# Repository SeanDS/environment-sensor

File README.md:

# environment-sensor
Ethernet-enabled dust particle, temperature and humidity sensor module

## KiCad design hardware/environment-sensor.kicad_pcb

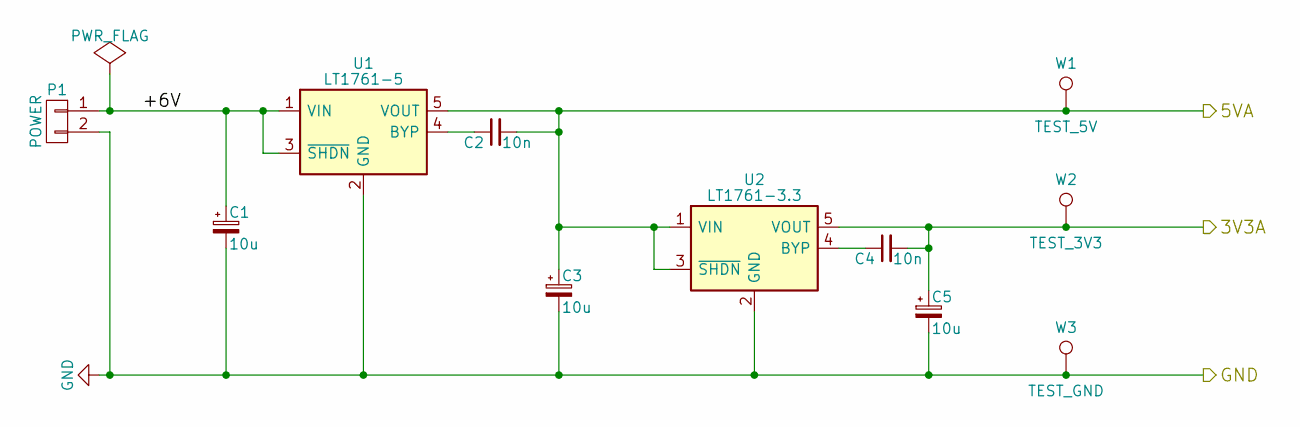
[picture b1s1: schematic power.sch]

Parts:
C1, C3, C5: 10u; C_Radial_D5_L11_P2
C2, C4: 10n; C_1206
P1: POWER; Molex_KK-6410-02_02x2.54mm_Straight
U1: LT1761-5; SOT-23-5
U2: LT1761-3.3; SOT-23-5
W1: TEST_5V; PINTST
W2: TEST_3V3; PINTST
W3: TEST_GND; PINTST

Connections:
/Microcontroller/3V3A: C4.2, C5.1, U2.5 (VOUT), W2.1; also elsewhere on the board
/Microcontroller/5VA: C2.2, C3.1, U1.5 (VOUT), U2.1 (VIN), U2.3 (~SHDN), W1.1; also elsewhere on the board
/Power Supply/+6V: C1.1, P1.1, U1.1 (VIN), U1.3 (~SHDN)
GND: C1.2, C3.2, C5.2, P1.2, U1.2 (GND), U2.2 (GND), W3.1; also elsewhere on the board
unnamed: C2.1, U1.4 (BYP)
unnamed: C4.1, U2.4 (BYP)

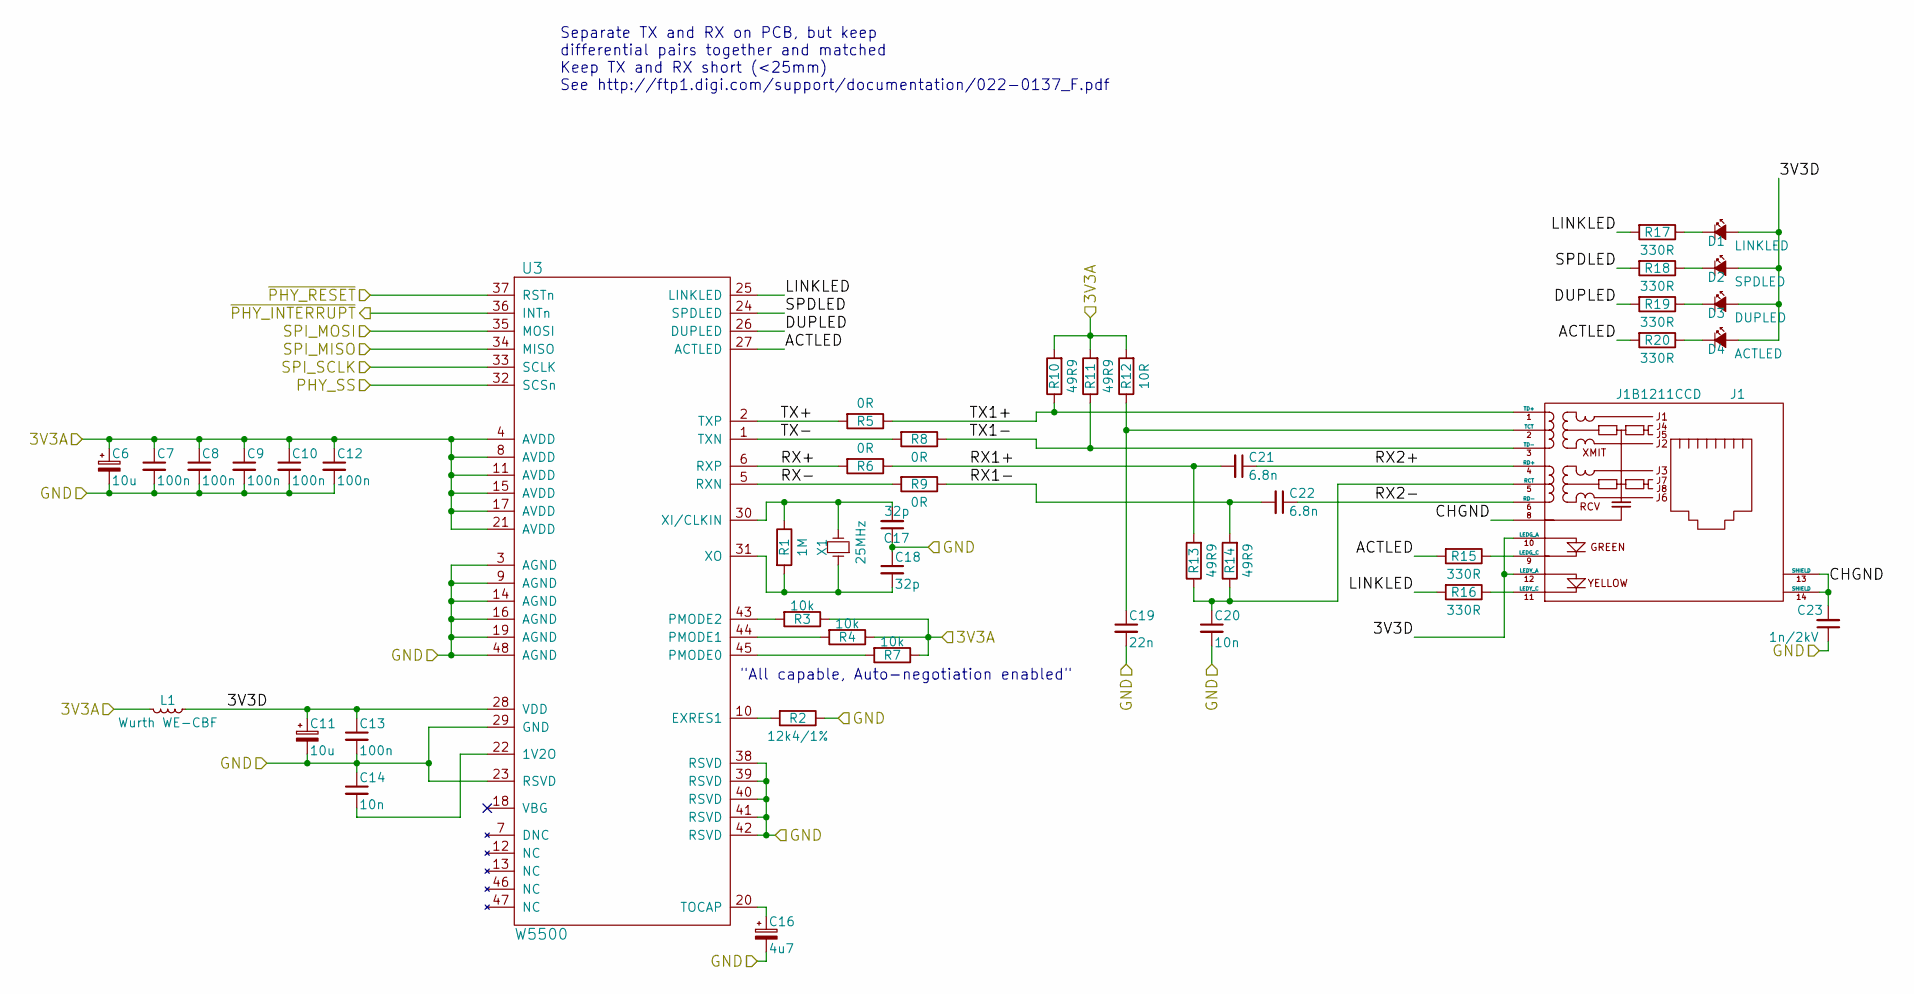
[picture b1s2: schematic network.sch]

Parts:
C6, C11: 10u; C_Radial_D5_L11_P2
C7, C8, C9, C10, C12, C13: 100n; C_1206
C14, C20: 10n; C_1206
C16: 4u7; C_Radial_D5_L11_P2
C17, C18: 32p; C_0603
C19: 22n; C_1206
C21, C22: 6.8n; C_1206
C23: 1n/2kV; C_1206
D1: LINKLED; LED_0805
D2: SPDLED; LED_0805
D3: DUPLED; LED_0805
D4: ACTLED; LED_0805
J1: J1B1211CCD; Cetus_J1B1211CCD
L1: Wurth WE-CBF; Choke_SMD_1206_Standard
R1: 1M; R_1206
R2: 12k4/1%; R_1206
R3, R4, R7: 10k; R_1206
R5, R6, R8, R9: 0R; R_1206
R10, R11, R13, R14: 49R9; R_1206
R12: 10R; R_1206
R15, R16, R17, R18, R19, R20: 330R; R_1206
U3: W5500; LQFP-48_7x7mm_Pitch0.5mm
X1: 25MHz; Crystal_HC49-SD_SMD

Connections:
/Microcontroller/3V3A: C6.1, C7.1, C8.1, C9.1, C10.1, C12.1, L1.2, R3.1, R4.1, R7.1, R10.2, R11.2, R12.2, U3.4 (AVDD), U3.8 (AVDD), U3.11 (AVDD), U3.15 (AVDD), U3.17 (AVDD), U3.21 (AVDD); also elsewhere on the board
/Microcontroller/PHY_SS: U3.32 (SCSn); also elsewhere on the board
/Microcontroller/SPI_MISO: U3.34 (MISO); also elsewhere on the board
/Microcontroller/SPI_MOSI: U3.35 (MOSI); also elsewhere on the board
/Microcontroller/SPI_SCLK: U3.33 (SCLK); also elsewhere on the board
/Microcontroller/~PHY_INTERRUPT: U3.36 (INTn); also elsewhere on the board
/Microcontroller/~PHY_RESET: U3.37 (RSTn); also elsewhere on the board
/Network I/O/3V3D: C11.1, C13.1, D1.2 (A), D2.2 (A), D3.2 (A), D4.2 (A), J1.10 (LEDG_A), J1.12 (LEDY_A), L1.1, U3.28 (VDD)
/Network I/O/ACTLED: R15.2, R20.2, U3.27 (ACTLED)
/Network I/O/CHGND: C23.2, J1.8, J1.13 (SHIELD), J1.14 (SHIELD)
/Network I/O/DUPLED: R19.2, U3.26 (DUPLED)
/Network I/O/LINKLED: R16.2, R17.2, U3.25 (LINKLED)
/Network I/O/RX1+: C21.2, R6.1, R13.2
/Network I/O/RX1-: C22.2, R9.1, R14.2
/Network I/O/RX2+: C21.1, J1.4 (RD+)
/Network I/O/RX2-: C22.1, J1.6 (RD-)
/Network I/O/RX+: R6.2, U3.6 (RXP)
/Network I/O/RX-: R9.2, U3.5 (RXN)
/Network I/O/SPDLED: R18.2, U3.24 (SPDLED)
/Network I/O/TX1+: J1.1 (TD+), R5.1, R10.1
/Network I/O/TX1-: J1.3 (TD-), R8.1, R11.1
/Network I/O/TX+: R5.2, U3.2 (TXP)
/Network I/O/TX-: R8.2, U3.1 (TXN)
GND: C6.2, C7.2, C8.2, C9.2, C10.2, C11.2, C12.2, C13.2, C14.1, C16.2, C17.1, C18.1, C19.2, C20.2, C23.1, R2.1, U3.3 (AGND), U3.9 (AGND), U3.14 (AGND), U3.16 (AGND), U3.19 (AGND), U3.23 (RSVD), U3.29 (GND), U3.38 (RSVD), U3.39 (RSVD), U3.40 (RSVD), U3.41 (RSVD), U3.42 (RSVD), U3.48 (AGND); also elsewhere on the board
unnamed: C14.2, U3.22 (1V2O)
unnamed: C16.1, U3.20 (TOCAP)
unnamed: C17.2, R1.1, U3.30 (XI/CLKIN), X1.2
unnamed: C18.2, R1.2, U3.31 (XO), X1.1
unnamed: C19.1, J1.2 (TCT), R12.1
unnamed: C20.1, J1.5 (RCT), R13.1, R14.1
unnamed: D1.1 (K), R17.1
unnamed: D2.1 (K), R18.1
unnamed: D3.1 (K), R19.1
unnamed: D4.1 (K), R20.1
unnamed: J1.9 (LEDG_C), R15.1
unnamed: J1.11 (LEDY_C), R16.1
unnamed: R2.2, U3.10 (EXRES1)
unnamed: R3.2, U3.43 (PMODE2)
unnamed: R4.2, U3.44 (PMODE1)
unnamed: R7.2, U3.45 (PMODE0)

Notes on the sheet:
"All capable, Auto-negotiation enabled"
Separate TX and RX on PCB, but keep differential pairs together and matched Keep TX and RX short (<25mm) See http://ftp1.digi.com/support/documentation/022-0137_F.pdf

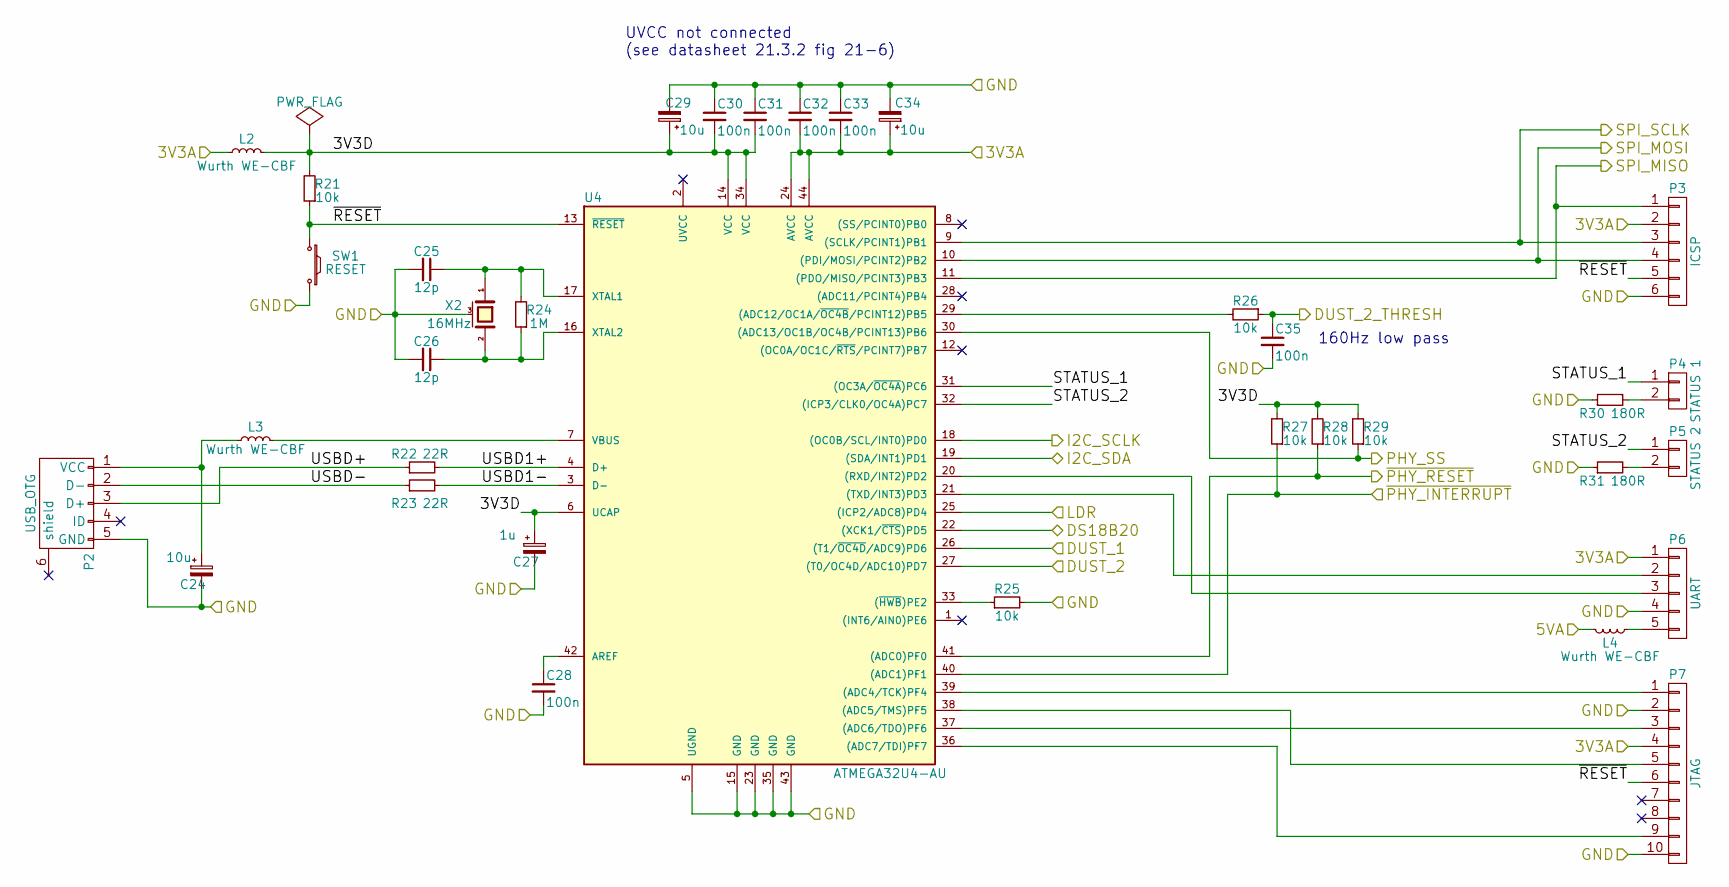
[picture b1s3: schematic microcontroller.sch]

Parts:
C24, C29, C34: 10u; C_Radial_D5_L11_P2
C25, C26: 12p; C_0603
C27: 1u; C_Radial_D5_L11_P2
C28, C30, C31, C32, C33, C35: 100n; C_1206
L2, L3, L4: Wurth WE-CBF; Choke_SMD_1206_Standard
P2: USB_OTG; USB_Micro-B_10103594-0001LF
P3: ICSP; Pin_Header_Straight_2x03
P4: STATUS 1; Molex_KK-6410-02_02x2.54mm_Straight
P5: STATUS 2; Molex_KK-6410-02_02x2.54mm_Straight
P6: UART; Pin_Header_Straight_1x05
P7: JTAG; Pin_Header_Straight_2x05_Pitch1.27mm
R21, R25, R26, R27, R28, R29: 10k; R_1206
R22, R23: 22R; R_1206
R24: 1M; R_1206
R30, R31: 180R; R_1206
SW1: RESET; SW_SPST_FSM_JSM; MPN1 4-1437565-1
U4: ATMEGA32U4-AU; TQFP-44_10x10mm_Pitch0.8mm
X2: 16MHz; crystal_FA238-TSX3225

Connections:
/Microcontroller/3V3A: C32.2, C33.2, C34.1, L2.1, P3.2, P6.1, P7.4, U4.24 (AVCC), U4.44 (AVCC); also elsewhere on the board
/Microcontroller/3V3D: C27.1, C29.1, C30.2, C31.2, L2.2, R21.2, R27.2, R28.2, R29.2, U4.6 (UCAP), U4.14 (VCC), U4.34 (VCC)
/Microcontroller/5VA: L4.2; also elsewhere on the board
/Microcontroller/DS18B20: U4.22 ((XCK1/~CTS~)PD5); also elsewhere on the board
/Microcontroller/DUST_1: U4.26 ((T1/~OC4D~/ADC9)PD6); also elsewhere on the board
/Microcontroller/DUST_2: U4.27 ((T0/OC4D/ADC10)PD7); also elsewhere on the board
/Microcontroller/DUST_2_THRESH: C35.1, R26.1; also elsewhere on the board
/Microcontroller/I2C_SCLK: U4.18 ((OC0B/SCL/INT0)PD0); also elsewhere on the board
/Microcontroller/I2C_SDA: U4.19 ((SDA/INT1)PD1); also elsewhere on the board
/Microcontroller/LDR: U4.25 ((ICP2/ADC8)PD4); also elsewhere on the board
/Microcontroller/PHY_SS: R29.1, U4.30 ((ADC13/OC1B/OC4B/PCINT13)PB6); also elsewhere on the board
/Microcontroller/SPI_MISO: P3.1, U4.11 ((PDO/MISO/PCINT3)PB3); also elsewhere on the board
/Microcontroller/SPI_MOSI: P3.4, U4.10 ((PDI/MOSI/PCINT2)PB2); also elsewhere on the board
/Microcontroller/SPI_SCLK: P3.3, U4.9 ((SCLK/PCINT1)PB1); also elsewhere on the board
/Microcontroller/STATUS_1: P4.1, U4.31 ((OC3A/~OC4A~)PC6)
/Microcontroller/STATUS_2: P5.1, U4.32 ((ICP3/CLK0/OC4A)PC7)
/Microcontroller/USBD1+: R22.2, U4.4 (D+)
/Microcontroller/USBD1-: R23.2, U4.3 (D-)
/Microcontroller/USBD+: P2.3 (D+), R22.1
/Microcontroller/USBD-: P2.2 (D-), R23.1
/Microcontroller/~PHY_INTERRUPT: R27.1, U4.40 ((ADC1)PF1); also elsewhere on the board
/Microcontroller/~PHY_RESET: R28.1, U4.41 ((ADC0)PF0); also elsewhere on the board
/Microcontroller/~RESET: P3.5, P7.6, R21.1, SW1.1, U4.13 (~RESET~)
GND: C24.2, C25.2, C26.2, C27.2, C28.2, C29.2, C30.1, C31.1, C32.1, C33.1, C34.2, C35.2, P2.5 (GND), P3.6, P6.4, P7.2, P7.10, R25.2, R30.1, R31.1, SW1.2, U4.5 (UGND), U4.15 (GND), U4.23 (GND), U4.35 (GND), U4.43 (GND), X2.3 (case); also elsewhere on the board
unnamed: C24.1, L3.1, P2.1 (VCC)
unnamed: C25.1, R24.2, U4.17 (XTAL1), X2.1
unnamed: C26.1, R24.1, U4.16 (XTAL2), X2.2
unnamed: C28.1, U4.42 (AREF)
unnamed: L3.2, U4.7 (VBUS)
unnamed: L4.1, P6.5
unnamed: P4.2, R30.2
unnamed: P5.2, R31.2
unnamed: P6.2, U4.21 ((TXD/INT3)PD3)
unnamed: P6.3, U4.20 ((RXD/INT2)PD2)
unnamed: P7.1, U4.39 ((ADC4/TCK)PF4)
unnamed: P7.3, U4.37 ((ADC6/TDO)PF6)
unnamed: P7.5, U4.38 ((ADC5/TMS)PF5)
unnamed: P7.9, U4.36 ((ADC7/TDI)PF7)
unnamed: R25.1, U4.33 ((~HWB~)PE2)
unnamed: R26.2, U4.29 ((ADC12/OC1A/~OC4B~/PCINT12)PB5)

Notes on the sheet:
160Hz low pass
UVCC not connected (see datasheet 21.3.2 fig 21-6)

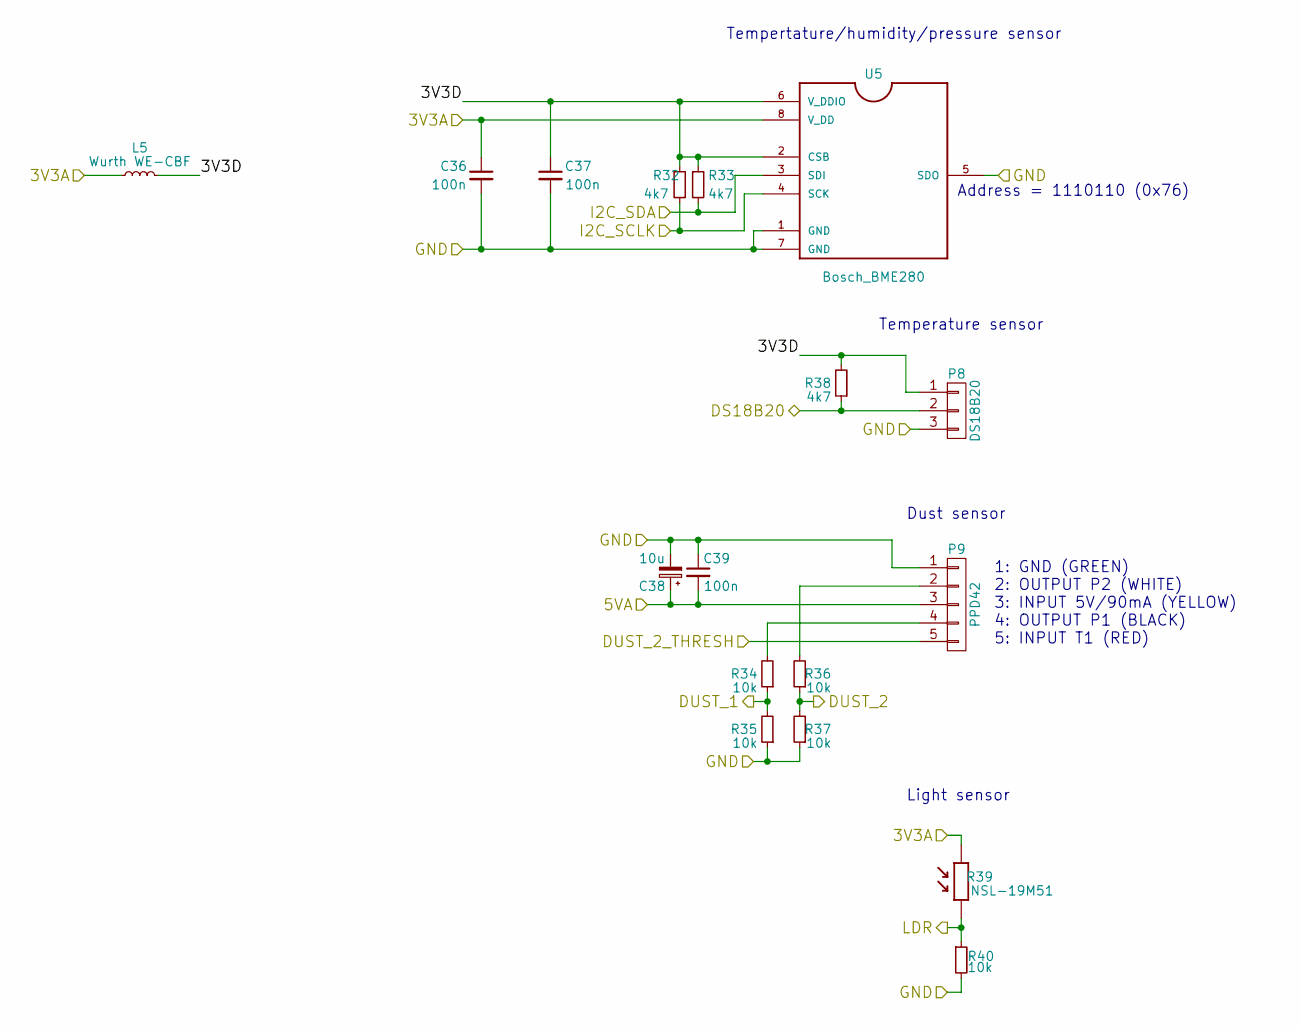
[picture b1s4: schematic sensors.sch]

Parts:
C36, C37, C39: 100n; C_1206
C38: 10u; C_Radial_D5_L11_P2
L5: Wurth WE-CBF; Choke_SMD_1206_Standard
P8: DS18B20; Molex_KK-6410-03_03x2.54mm_Straight
P9: PPD42; Molex_KK-6410-05_05x2.54mm_Straight
R32, R33, R38: 4k7; R_1206
R34, R35, R36, R37, R40: 10k; R_1206
R39: NSL-19M51; NSL_19M51; MPN1 NSL-19M51
U5: Bosch_BME280; Bosch_BME280_LGA-8

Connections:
/Microcontroller/3V3A: C36.1, L5.1, R39.2, U5.8 (V_DD); also elsewhere on the board
/Microcontroller/5VA: C38.1, C39.2, P9.3; also elsewhere on the board
/Microcontroller/DS18B20: P8.2, R38.1; also elsewhere on the board
/Microcontroller/DUST_1: R34.1, R35.2; also elsewhere on the board
/Microcontroller/DUST_2: R36.1, R37.2; also elsewhere on the board
/Microcontroller/DUST_2_THRESH: P9.5; also elsewhere on the board
/Microcontroller/I2C_SCLK: R32.2, U5.4 (SCK); also elsewhere on the board
/Microcontroller/I2C_SDA: R33.2, U5.3 (SDI); also elsewhere on the board
/Microcontroller/LDR: R39.1, R40.1; also elsewhere on the board
/Sensors/3V3D: C37.1, L5.2, P8.1, R32.1, R33.1, R38.2, U5.2 (CSB), U5.6 (V_DDIO)
GND: C36.2, C37.2, C38.2, C39.1, P8.3, P9.1, R35.1, R37.1, R40.2, U5.1 (GND), U5.5 (SDO), U5.7 (GND); also elsewhere on the board
unnamed: P9.2, R36.2
unnamed: P9.4, R34.2

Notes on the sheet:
Address = 1110110 (0x76)
1: GND (GREEN) 2: OUTPUT P2 (WHITE) 3: INPUT 5V/90mA (YELLOW) 4: OUTPUT P1 (BLACK) 5: INPUT T1 (RED)
Dust sensor
Light sensor
Tempertature/humidity/pressure sensor
Temperature sensor

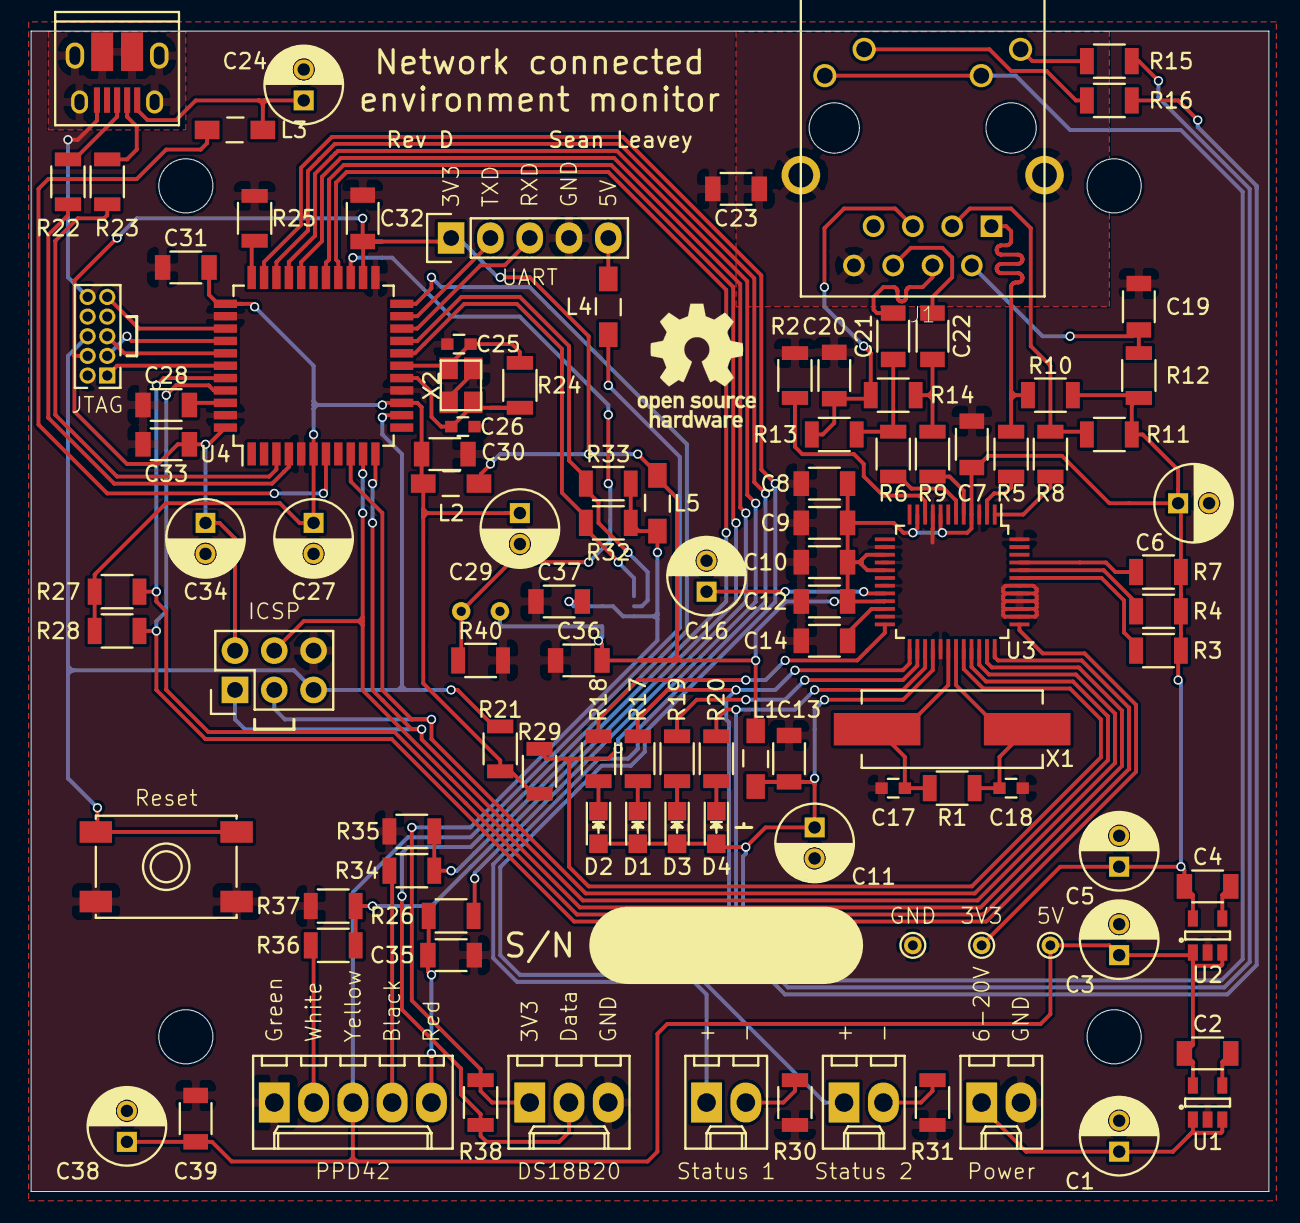
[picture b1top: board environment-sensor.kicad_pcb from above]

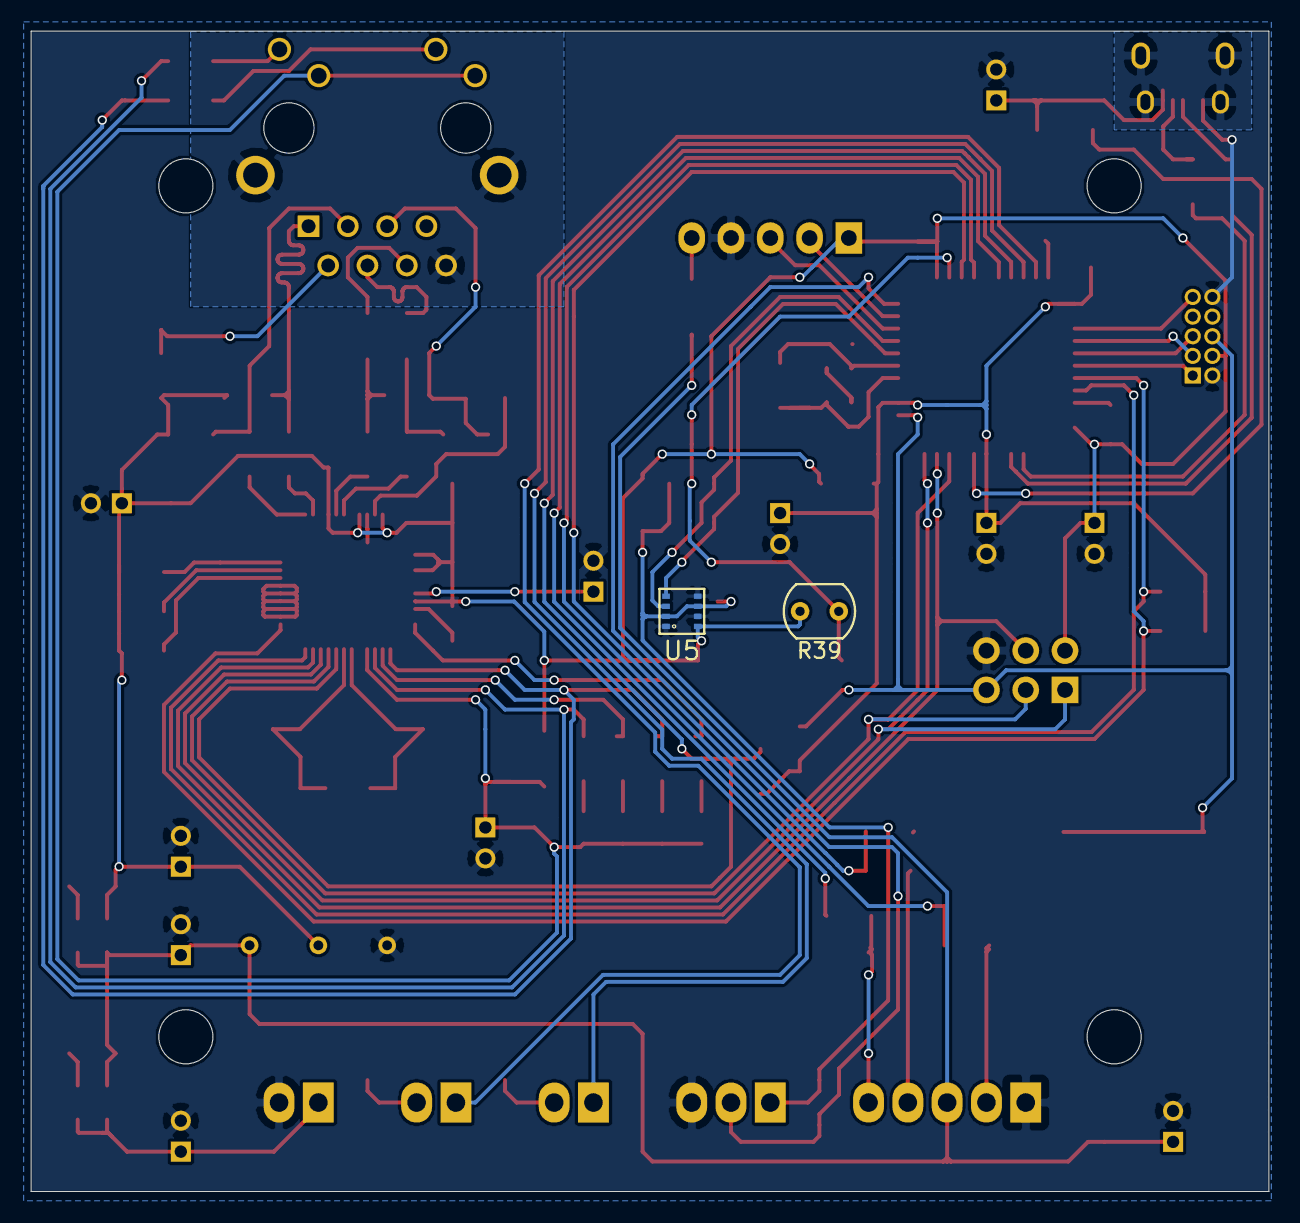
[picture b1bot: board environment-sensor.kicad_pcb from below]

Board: 2 copper layers, 80.0 x 75.0 mm, 109 parts (2 on the bottom side), 78 nets.

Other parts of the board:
Ref**: Val**; 80mmx75mm_holes

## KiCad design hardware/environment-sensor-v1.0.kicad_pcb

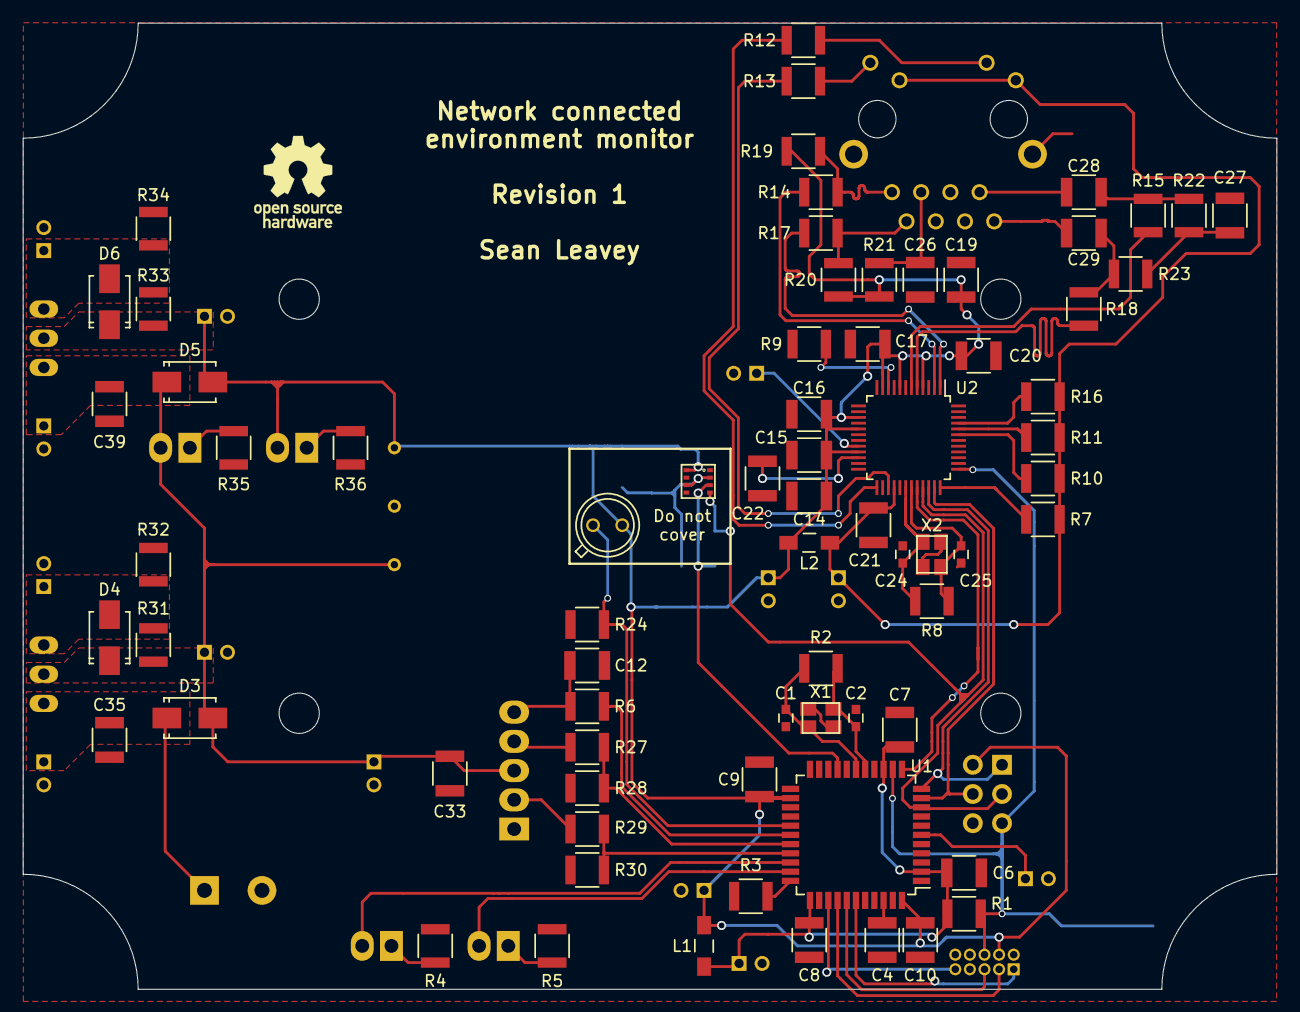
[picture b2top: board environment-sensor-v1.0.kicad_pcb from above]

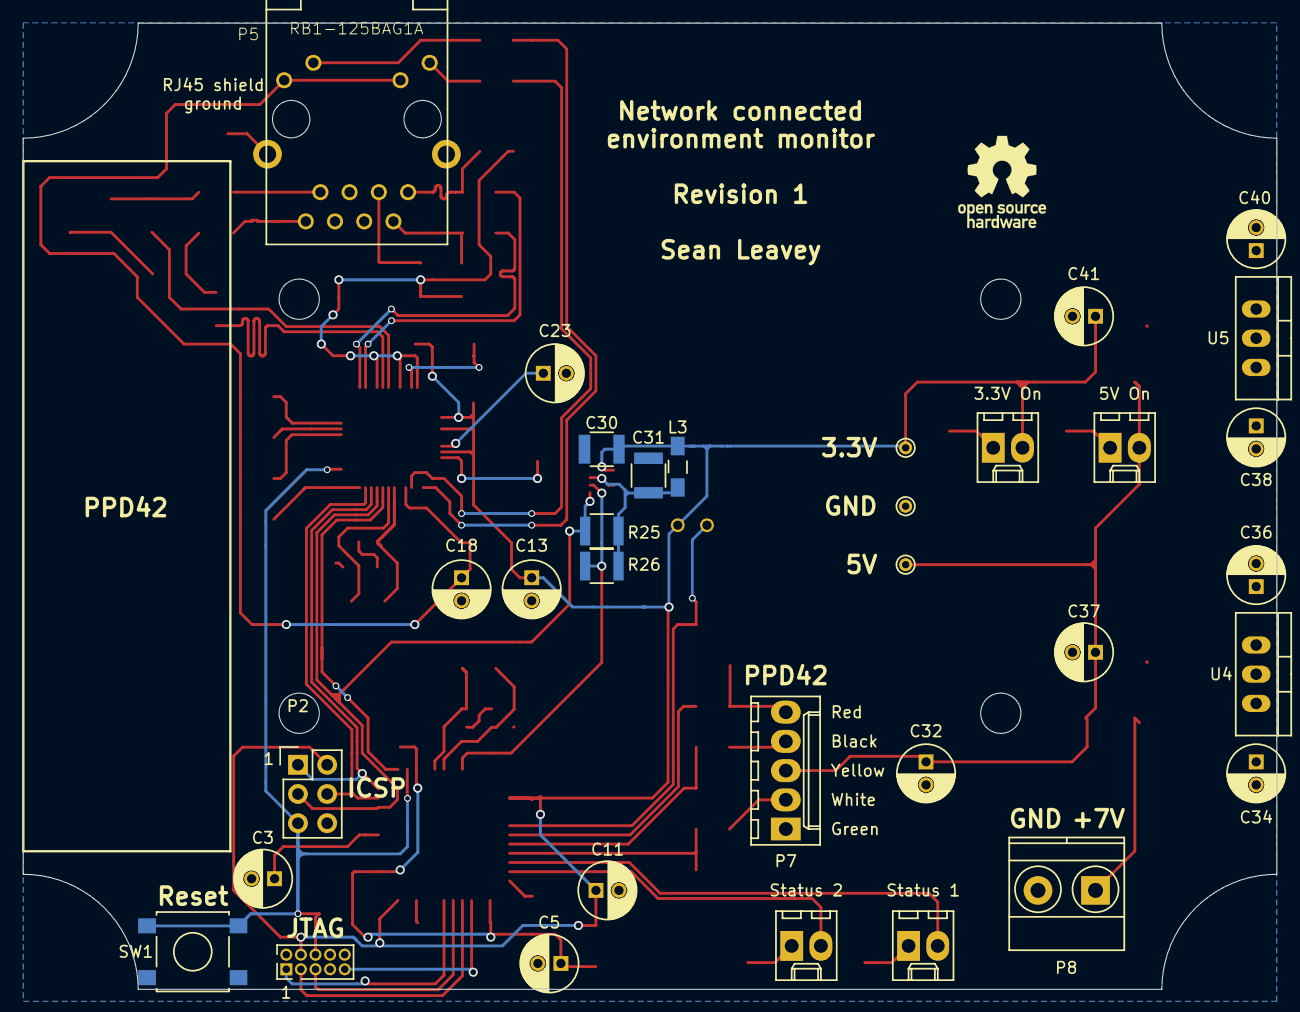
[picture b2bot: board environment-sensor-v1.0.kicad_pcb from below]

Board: 2 copper layers, 109.0 x 84.0 mm, 106 parts (33 on the bottom side), 62 nets.

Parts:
C1, C2, C24, C25: 12p; C_0603
C3, C5, C11, C13, C18, C32, C34, C36, C37, C38, C40, C41: 10u; C_Radial_D5_L11_P2
C4, C6, C7, C8, C9, C10, C12, C14, C15, C16, C17, C19, C20, C21, C26, C30, C31, C33, C35, C39: 100n; C_1210
C22, C27, C28, C29: 10n; C_1210
C23: 4u7; C_Radial_D5_L11_P2
D1: Status 1; Molex_KK-6410-02_02x2.54mm_Straight
D2: Status 2; Molex_KK-6410-02_02x2.54mm_Straight
D3, D4, D5, D6: S1B-13-F; SMA_Standard
D7: LED_5V; Molex_KK-6410-02_02x2.54mm_Straight
D8: LED_3V3; Molex_KK-6410-02_02x2.54mm_Straight
L1, L2, L3: Wurth WE-CBF; Choke_SMD_1206_Standard
P2: ICSP; Pin_Header_Straight_2x03
P4: JTAG; Pin_Header_Straight_2x05_Pitch1.27mm
P5: RB1-125BAG1A; WIZNET_RB1-125BAG1A
P6: NSL-19M51; TO-18_2Pin
P7: PPD42; Molex_KK-6410-05_05x2.54mm_Straight
P8: POWER; TerminalBlock_Pheonix_MKDS1.5-2pol
R1, R3, R6, R7, R10, R11, R16, R24, R27, R28, R29, R30: 10k; R_1210
R2, R8: 1M; R_1210
R4, R5, R34, R36: 180R; R_1210
R9: 12k4/1%; R_1210
R12, R13, R32: 330R; R_1210
R14, R15, R17, R18: 33R; R_1210
R19, R20, R22, R23: 49R9/1%; R_1210
R21: 10R/1%; R_1210
R25, R26: 4k7; R_1210
R31, R33: 110R; R_1210
R35: 270R; R_1210
Ref**: Val**; 109mmx84mm_holes
SW1: Reset; SW_SPST_B3S-1000
U1: ATMEGA32U4-AU; TQFP-44_10x10mm_Pitch0.8mm
U2: W5500; LQFP-48_7x7mm_Pitch0.5mm
U3: Bosch_BME280; Bosch_BME280_LGA-8
U4, U5: LM317T; TO-220_Neutral123_Vertical
W1: TEST_5V; PINTST
W2: TEST_3V3; PINTST
W3: TEST_GND; PINTST
X1: 16MHz; crystal_FA238-TSX3225
X2: 25MHz; crystal_FA238-TSX3225

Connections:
/Microcontroller/3V3A: C9.2, C10.2, C11.1, C13.1, C14.1, C15.1, C16.1, C17.1, C19.1, C20.1, C30.1, C41.1, D5.2, D6.1, D8.2, L1.1, L2.1, L3.1, P2.2, P4.4, P6.1, R19.2, R20.2, R21.2, R33.1, U1.24, U1.44, U2.4, U2.8, U2.11, U2.15, U2.17, U2.21, U3.8, U5.2, W2.1
/Microcontroller/3V3D: C5.1, C6.2, C7.2, C8.2, L1.2, R1.1, U1.2, U1.14, U1.34
/Microcontroller/LDR_OUT: P6.2, R24.1, U1.27
/Microcontroller/MISO: P2.1, U1.11, U2.34
/Microcontroller/MOSI: P2.4, U1.10, U2.35
/Microcontroller/P_OUT_1: R27.1, R28.2, U1.29
/Microcontroller/P_OUT_2: R29.1, R30.2, U1.30
/Microcontroller/P_THRESH: C12.1, P7.5, R6.1
/Microcontroller/SCLK: P2.3, R25.2, U1.9, U2.33, U3.4
/Microcontroller/SDA: R26.2, U1.19, U3.3
/Microcontroller/SS_PHY: U1.12, U2.32
/Microcontroller/~RESET: P2.5, P4.6, R1.2, SW1.1, U1.13, U2.37
/Network I/O/3V3D: C18.1, C21.1, L2.2, P5.L1, P5.L3, R7.1, R10.1, R11.1, R16.1, U2.28
/Network I/O/ACTLED: P5.L4, R13.1
/Network I/O/LINKLED: P5.L2, R12.1
/Network I/O/RX1+: C28.2, R15.1, R22.2
/Network I/O/RX1-: C29.2, R18.1, R23.2
/Network I/O/RX2+: C28.1, P5.R7
/Network I/O/RX2-: C29.1, P5.R8
/Network I/O/RX+: R15.2, U2.6
/Network I/O/RX-: R18.2, U2.5
/Network I/O/TX1+: P5.R1, R14.1, R19.1
/Network I/O/TX1-: P5.R2, R17.1, R20.1
/Network I/O/TX+: R14.2, U2.2
/Network I/O/TX-: R17.2, U2.1
/Power Supply/5VA: C32.1, C33.2, C37.1, C38.1, C39.1, D3.2, D4.1, D5.1, D7.2, P7.3, R31.1, U4.2, U5.3, W1.1
/Power Supply/+6V: C34.1, C35.1, D3.1, P8.1, U4.3
/Sensors/3V3D: C31.1, L3.2, R25.1, R26.1, U3.2, U3.6
GND: C1.2, C2.2, C3.2, C4.2, C5.2, C6.1, C7.1, C8.1, C9.1, C10.1, C11.2, C12.2, C13.2, C14.2, C15.2, C16.2, C17.2, C18.2, C19.2, C20.2, C21.2, C22.1, C23.2, C24.1, C25.1, C26.2, C27.2, C30.2, C31.2, C32.2, C33.1, C34.2, C35.2, C36.2, C37.2, C38.2, C39.2, C40.2, C41.2, P2.6, P4.2, P4.10, P7.1, P8.2, R3.1, R4.1, R5.1, R9.1, R24.2, R28.1, R30.1, R32.2, R34.2, R35.2, R36.2, SW1.2, U1.5, U1.15, U1.23, U1.35, U1.43, U2.3, U2.9, U2.14, U2.16, U2.19, U2.29, U2.48, U3.1, U3.5, U3.7, W3.1, X1.3, X2.3
unnamed: C1.1, R2.1, U1.17, X1.1
unnamed: C2.1, R2.2, U1.16, X1.2
unnamed: C3.1, U1.6
unnamed: C4.1, U1.42
unnamed: C22.2, U2.22
unnamed: C23.1, U2.20
unnamed: C24.2, R8.1, U2.30, X2.2
unnamed: C25.2, R8.2, U2.31, X2.1
unnamed: C26.1, P5.R3, R21.1
unnamed: C27.1, R22.1, R23.1
unnamed: C36.1, D4.2, R31.2, R32.1, U4.1
unnamed: C40.1, D6.2, R33.2, R34.1, U5.1
unnamed: D1.1, R4.2
unnamed: D1.2, U1.31
unnamed: D2.1, R5.2
unnamed: D2.2, U1.32
unnamed: D7.1, R35.1
unnamed: D8.1, R36.1
unnamed: P4.1, U1.39
unnamed: P4.3, U1.37
unnamed: P4.5, U1.38
unnamed: P4.9, U1.36
unnamed: P7.2, R29.2
unnamed: P7.4, R27.2
unnamed: R3.2, U1.33
unnamed: R6.2, U1.28
unnamed: R7.2, U2.36
unnamed: R9.2, U2.10
unnamed: R10.2, U2.43
unnamed: R11.2, U2.44
unnamed: R12.2, U2.25
unnamed: R13.2, U2.27
unnamed: R16.2, U2.45

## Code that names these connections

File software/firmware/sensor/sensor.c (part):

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uint32_t pulse_2 = 0;

// dust measurements
volatile uint16_t dust_1 = 0;
volatile uint16_t dust_2 = 0;

void set_led_1(uint8_t flag) {
	led_1_status = flag;
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}

void wizchip_enable(void) {
	PORTF |= (1 << PF0);
}

void wizchip_disable(void) {
	PORTF &= ~(1 << PF0);
}

void wizchip_cycle(void) {
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}

void wizchip_select(void) {
	PORTB &= ~(1 << PB6);
}

void wizchip_deselect(void) {
	PORTB |= (1 << PB6);
}

void general_timer_enable(void) {
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
	// measure dust triggers: add 1 if the dust sensor output is pulled low
	// (indicating dust), else add 0
	pulse_1 += (PIND & (1 << PD6)) == 0 ? 1 : 0;
	pulse_2 += (PIND & (1 << PD7)) == 0 ? 1 : 0;

	// approx 30 seconds
	if (dust_timer_ovf_count > 930) {
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
	// every 32.768 ms
	if (led_1_status == LED_ON) {
		PORTC |= (1 << PC6);
	} else if (led_1_status == LED_OFF) {
		PORTC &= ~(1 << PC6);
	}

	// every 32.768 ms
	if (led_2_status == LED_ON) {
		PORTC |= (1 << PC7);
	} else if (led_2_status == LED_OFF) {
		PORTC &= ~(1 << PC7);
	}

	// approx every 500 ms
	if (led_timer_ovf_count >= 15) {
		if (led_1_status == LED_FLASHING) {
			// toggle LED
			PORTC ^= (1 << PC6);
		}

		if (led_2_status == LED_FLASHING) {
			// toggle LED
			PORTC ^= (1 << PC7);
		}

		// reset counter
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
	if (pwm_timer_ovf_count >= 16) {
		// switch on
		PORTB |= (1 << PB5);
	} else {
		// switch off
		PORTB &= ~(1 << PB5);
	}

	if (pwm_timer_ovf_count >= 16) {
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	clock_prescale_set(clock_div_8);

	// set W5500 chip select as output
	DDRB |= (1 << PB6);

	// set W5500 reset line as output
	DDRF |= (1 << PF0);

	// set LED pins as outputs
	DDRC |= (1 << PC6);
	DDRC |= (1 << PC7);

	// turn off LEDs
	set_led_1(LED_OFF);
	set_led_2(LED_OFF);

	// set dust sensor P1 and P2 inputs
	DDRD &= ~(1 << PD6);
	DDRD &= ~(1 << PD7);

	// set dust sensor threshold as output
	DDRB |= (1 << PB5);

	// disable W5500 chip select
    wizchip_deselect();
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
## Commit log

2017-04-17 Work on schematic
2017-05-01 Replace Wiznet legacy model with updated one
2017-05-01 Almost finished layout
2017-05-01 Add planes for regulators
2017-05-02 Move labels, replace some SMB diodes with SMA, final tweaks
2017-05-02 Move LM317 regulator footprints to underside; final tweaks
2017-05-02 Add licence
    CC-BY-SA 4.0
2017-06-20 Revision of board to address issues
2017-06-21 Small update to board
2017-06-21 Board files for revision 2
2017-08-14 Further update to change clock package and move some components around
2017-08-20 Revision to address clock issue
2017-09-26 Sensor readout code using virtual serial over USB
2017-09-26 Rename USB firmware
2017-09-29 Working example with DHCP, USB debugging and analog/digital sensor readings. Problem with USB in that it crashes if too much stuff is done in between calls to USB_USBTask(). Will investigate alternat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
2017-09-29 Example with USB debugging via minimal Teensy library
2017-10-02 Working DHCP, sensor readouts and USB serial
2017-10-02 USB line printer with carriage return; PWM output for dust sensor; cleanup
2017-10-02 Python3 listener for testing messaging
2017-10-02 Working communication
2017-10-04 Remove custom USB functions and instead redirect stdin/stdout to USB
2017-10-04 Move data timer overflow counter into its own loop
2017-10-04 Formatted payload
2017-10-05 JSON encoded sensor data; smaller buffers; better memory use
2017-10-05 Remove abuse of NULL for int function parameter
2017-10-06 Socket no longer closed during normal operation - this is reserved for errors since it generates [RST, ACK] TCP flags as opposed to e.g. [FIN, ACK].
2017-10-06 Add required Content-Length header
2017-10-09 Update footprints and parts
2017-10-10 New revision to board
2017-10-11 Finishing tweaks to revision 4
2017-10-11 Board files for revision 4
2017-10-11 Board files for revision 3 (from August)
2017-10-11 Board files for revision 3
2017-10-12 Added some part numbers to the schematic
2017-11-01 Disable W5500 in startup, enable before use
2017-11-01 Add required stdio header (previously imported via bme280.h)
2017-11-01 Change PWM port for dust sensor threshold
2017-11-02 Clean up sensor code
2017-11-03 Add comments; non-functional refactoring
2017-11-03 Add LED and DHCP reset functionality
    Blinking LED states now used to indicate DHCP status; DHCP retries now infinite.
2017-11-03 Fix bug with LEDs when physical link is disconnected after startup
2017-11-04 Change frequency division to 8 to avoid being out of specification
    It turns out that the ATMEGA32U4's safe operating area for 16 MHz (which is what the crytal provides) is defined
    for voltages over 4.5 V (see p386, figure 29-2 of datasheet). Since we use 3.3 V, the clock should be divided by
    at least 2 to stay within safe operation. I chose here to divide by 8 to avoid excess heat generation.
2017-11-05 Update interrupts to more closely match 1s intervals
2017-11-29 Fix use of string version as float in JSON string
2017-11-30 Fix other bug with float
2018-11-12 Measure every 30 seconds
2018-11-12 Refactor some logic blocks
2018-11-12 Add host to HTTP GET request
